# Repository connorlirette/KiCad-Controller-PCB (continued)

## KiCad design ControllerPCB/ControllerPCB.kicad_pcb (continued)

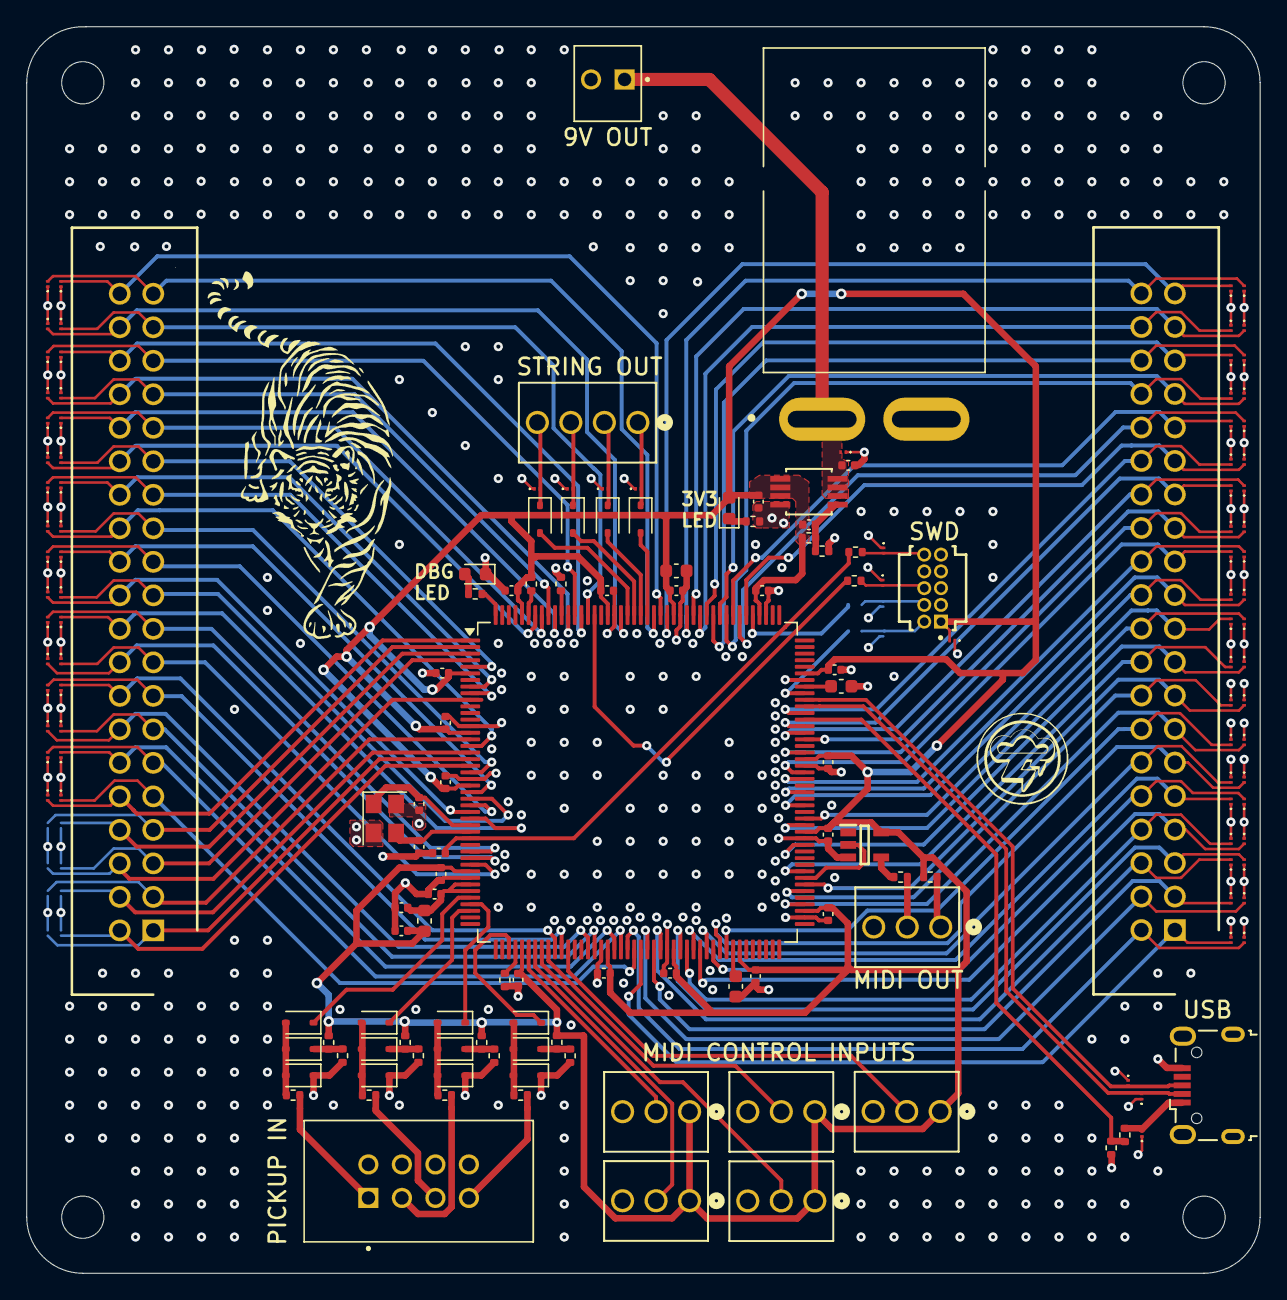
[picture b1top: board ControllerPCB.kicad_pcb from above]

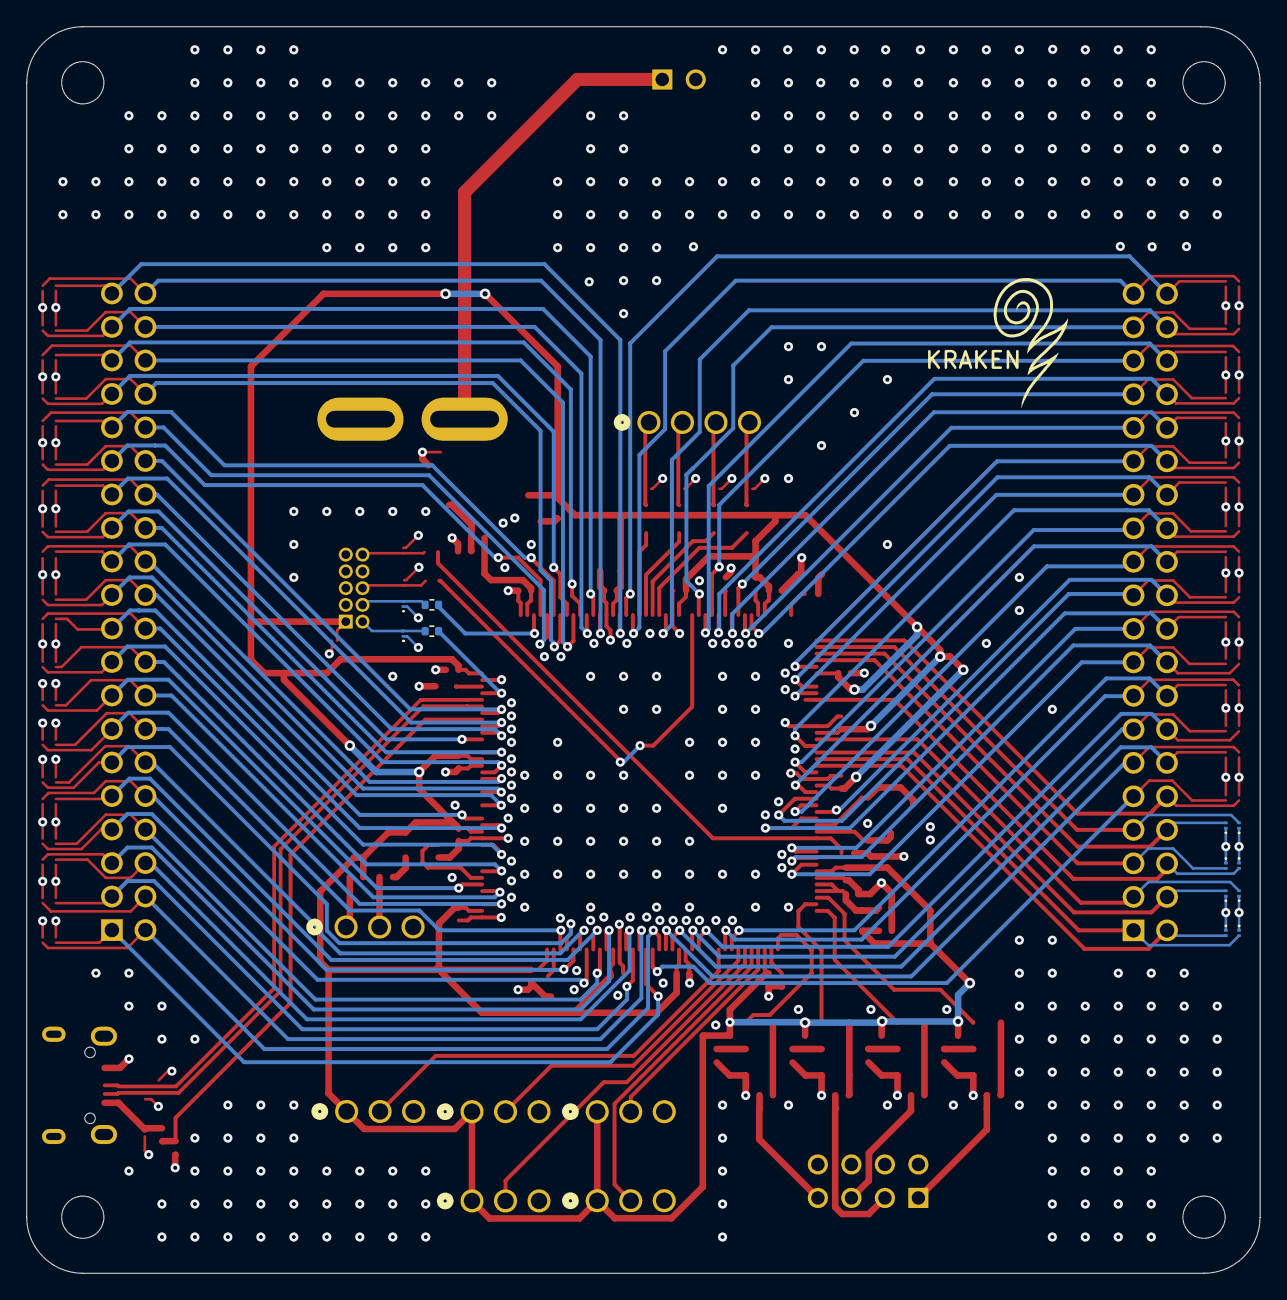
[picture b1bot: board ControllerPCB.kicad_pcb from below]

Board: 4 copper layers, 93.5 x 94.5 mm, 189 parts (12 on the bottom side), 140 nets.

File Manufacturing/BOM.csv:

"Value","Reference","Footprint","JLCPCB Part #"
"10u","C101","Capacitor_SMD:C_0603_1608Metric","C19702"
"100n","C102,C103,C104,C105,C106,C107,C109,C110,C111,C113,C115,C116,C118,C119","Capacitor_SMD:C_0402_1005Metric","C1525 "
"12p","C108,C112","Capacitor_SMD:C_0402_1005Metric","C161304"
"2.2u","C114,C117","Capacitor_SMD:C_0603_1608Metric","C99228 "
"10n","C120","Capacitor_SMD:C_0402_1005Metric","C60133"
"1u","C121,C122,C201,C203","Capacitor_SMD:C_0402_1005Metric","C52923"
"100p","C202","Capacitor_SMD:C_0402_1005Metric","C1546"
"BLUE","D101","LED_SMD:LED_0603_1608Metric","C2288"
"D_TVS_Small","D102,D103,D104,D105,D106,D107,D108,D110,D111,D112,D117,D201,D501,D502,D503,D504,D505,D506,D507,D508,D509,D510,D511,D512,D513,D514,D515,D516,D517,D518,D519,D520,D521,D522,D523,D524,D525,D526,D527,D528,D529,D530,D531,D532,D533,D534,D535,D536,D537,D538,D539,D540,D541,D542,D543,D544,D545,D546,D547,D548,D549,D550,D551,D552,D553,D554,D555,D556,D557,D558,D559,D560,D561,D562,D563,D564,D565,D566,D567,D568,D569,D570,D571,D572,D573,D574,D575,D576,D577,D578,D579,D580","0_Footprint_lib:PMEG3005AESFYL","C2908830"
"D_TVS_VBUS","D109","0_Footprint_lib:PMEG3005AESFYL","C2443412"
"D_Small","D113,D114,D115,D116,D401,D402,D403,D404,D405,D406,D407,D408,D409,D410,D411,D412","Diode_SMD:D_SOD-323","C146335"
"GRN","D202","LED_SMD:LED_0603_1608Metric","C22371297"
"120R","FB101","Inductor_SMD:L_0603_1608Metric","C113030"
"1k","R101,R203,R401,R402,R407,R410","Resistor_SMD:R_0402_1005Metric","C11702 "
"10k","R102,R103","Resistor_SMD:R_1206_3216Metric","C17902"
"22R","R104,R105,R106,R107","Resistor_SMD:R_0402_1005Metric","C25092"
"33k","R108","Resistor_SMD:R_0402_1005Metric","C25779"
"82k","R109","Resistor_SMD:R_0402_1005Metric","C4142"
"140k","R201","Resistor_SMD:R_0402_1005Metric","C2998127"
"78.7k","R202","Resistor_SMD:R_0402_1005Metric","C852915"
"33R","R301","Resistor_SMD:R_0402_1005Metric","C25105"
"10R","R302","Resistor_SMD:R_0402_1005Metric","C25077"
"220","R403,R405,R408,R411","Resistor_SMD:R_0402_1005Metric","C25091"
"2k","R404,R406,R409,R412","Resistor_SMD:R_0402_1005Metric","C4109"
"74LVC1G17","U301","0_Footprint_lib:SOT95P280X145-5N","C7836"
"16MHz","Y101","Crystal:Crystal_SMD_3225-4Pin_3.2x2.5mm","C13738"

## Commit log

2025-02-11 initial test commit
2025-02-11 test commit 2
2025-02-11 Added footprints to the resistors and capacitors and values of Crystall Oscillator capacitors.
2025-02-11 grant test commit
2025-02-17 Power_Connector
    Power portion added
2025-02-18 rev 0.1
    - power and amplitude sheets added
2025-02-20 symbol update
2025-02-21 updated Amplitude_Detection_sch.kicad_sch
2025-03-06 rev 0.1 - Redid the GPIO pinouts and removed the CLRs. - Split the 80 pin conn into two 40 pin conns - Added conn and pinouts for SWD - Added conn and pinouts for USB_FS over USB Micro B - Added conn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
2025-03-07 Redid the power supply schematic. Controller now powered from the 5V supply from the usb VBUS. Also added EMD suppression TVS diode to the VBUS line to avoid any possible voltage surge.
2025-03-08 Split the MIDI controls connector into 5 3-pin connectors. Added an extra MIDI controls connector in case we want to add another control. Added the 1x4 string output connector.
2025-03-08 Updated many things.
2025-03-08 Added midi_out and amp_detections schematics
2025-03-08 Added VCAP 1/2 capacitors. These assist the internal voltage regulator. We don't have an option to turn the regulator off so it is always on.
    Swapped the crystal oscillator out for a different one.
    Tweaked the VREF+ scheme a bit - changed the 100nF decoupling cap to 10nF to comply with the datasheet when VREF+ is connected to VDDA
2025-03-09 Organized the schematic a bit
2025-03-09 Created a stm32cubeide project with the exact pinout of the controller schematic. Double checked the pinouts and renamed the 80 inputs to be input_# for readability
2025-03-10 Began the PCB. Placed the decoupling caps, usb micro b conn and others. Adding footprints for components as well.
2025-03-10 test
2025-03-12 Added separate sheet for IO. Added TVS diodes for every external input to the controller except for the ADC and MIDI control inputs. Still need to add decoupling caps for the 9V humbucker source. Par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
2025-03-17 rev 0.3
2025-03-18 rev 0.4
2025-03-20 rev 1.0
2025-03-20 rev 1.01 added "manufacturing" folder - keep the gerber and manufacturing files in here
2025-03-22 rev1.02
2025-03-22 rev 1.04
    - gerbers/BOM/CPL files are all generated.
2025-03-25 rev 1.05
    - new controller is used.
    - updated the pcb layout
